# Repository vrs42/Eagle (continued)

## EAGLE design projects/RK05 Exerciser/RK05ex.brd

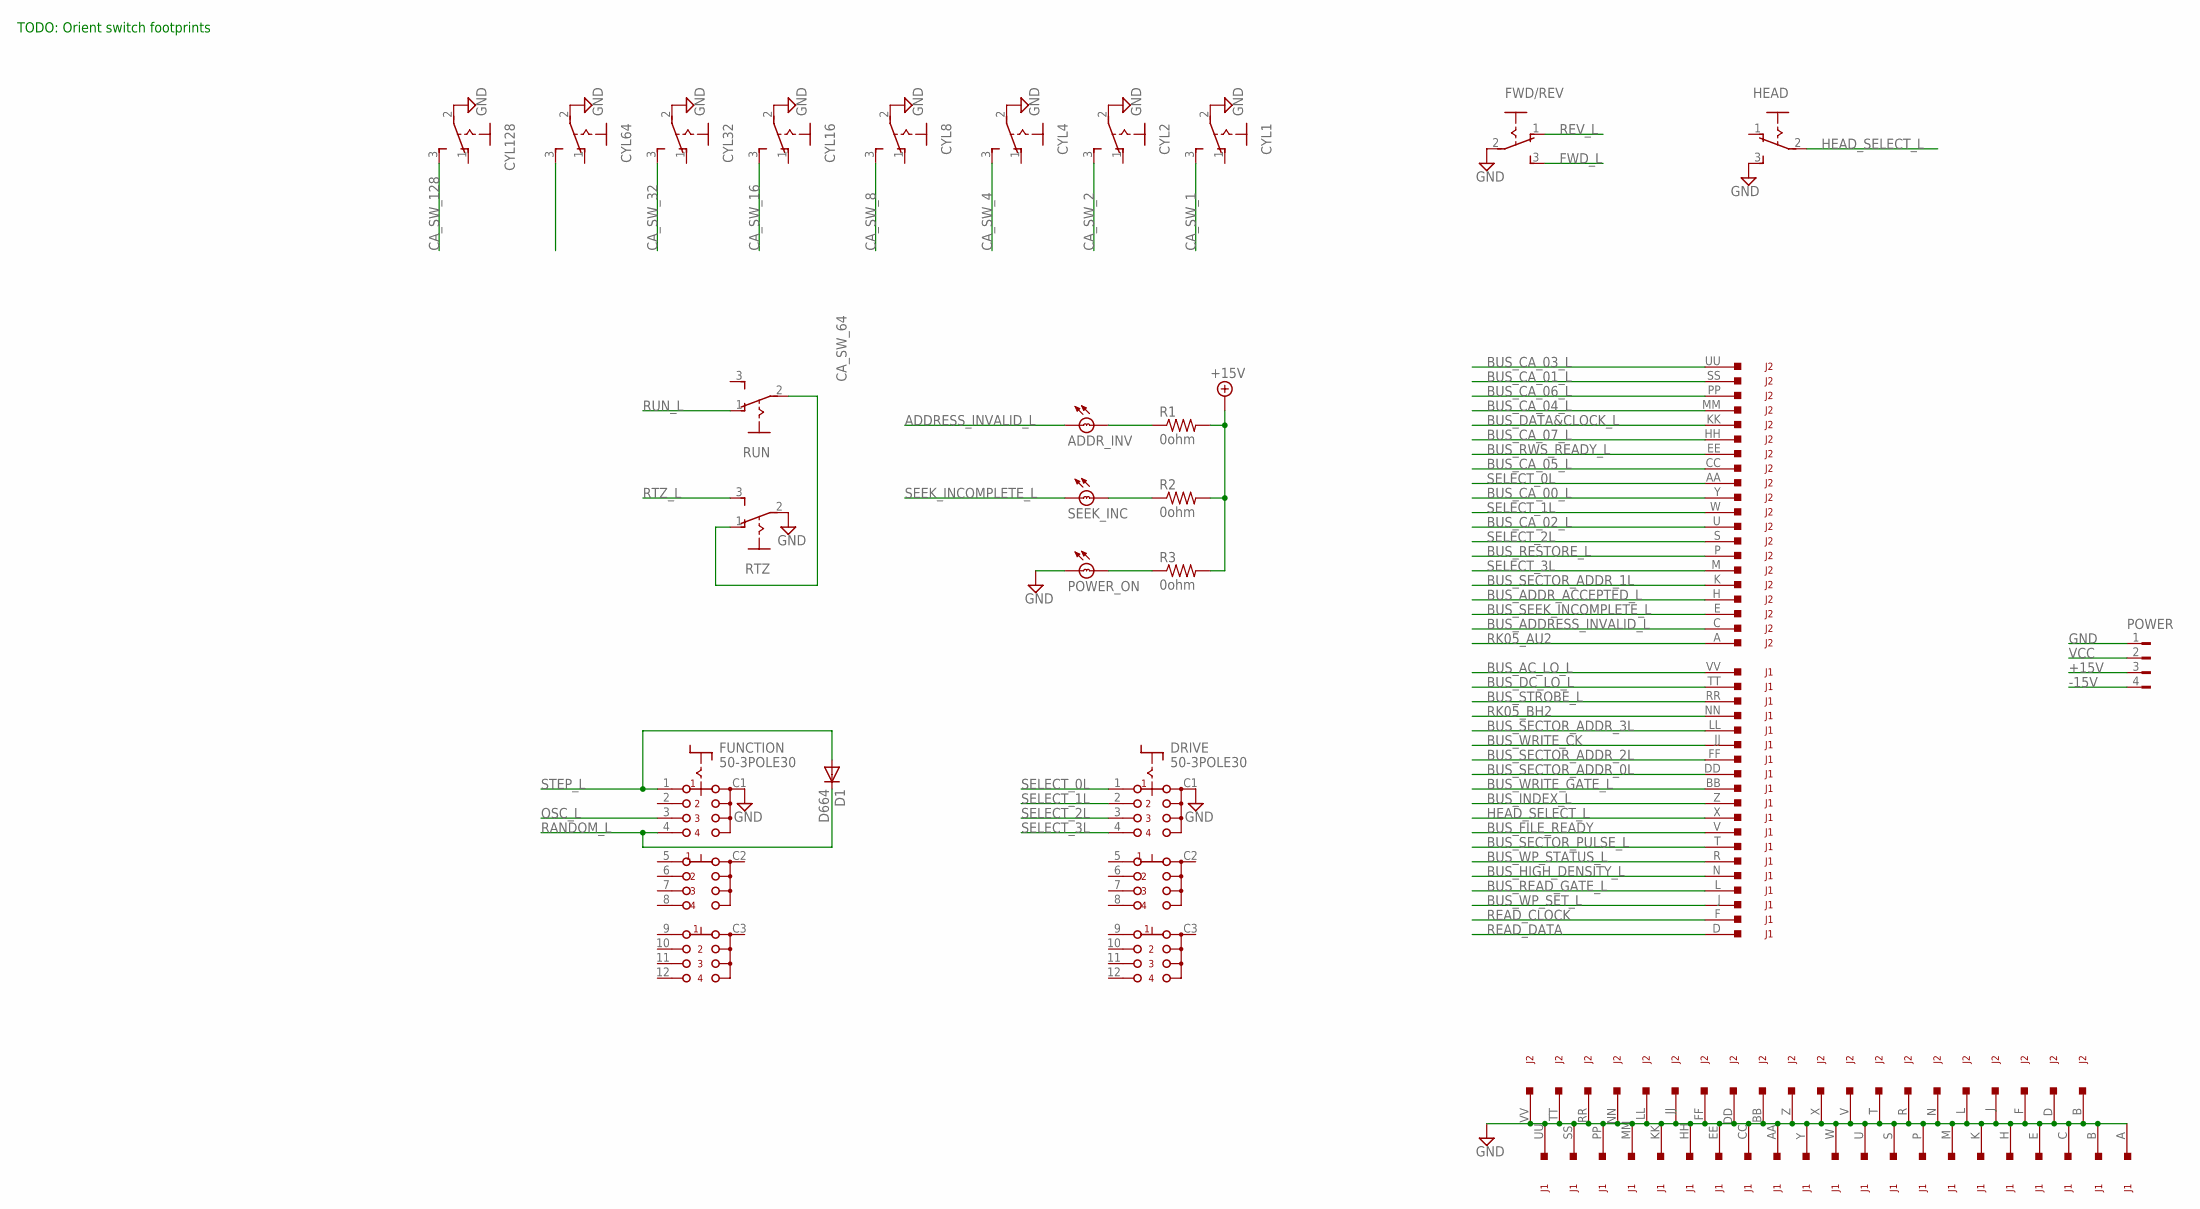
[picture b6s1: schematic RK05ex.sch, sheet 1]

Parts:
ADDR_INV: BULB
CYL1, CYL2, CYL4, CYL8, CYL16, CYL32, CYL64, CYL128: 255SB
D1: D664; DO35-10
DRIVE: 50-3POLE30
FUNCTION: 50-3POLE30
FWD/REV: 255SB
HEAD: 255SB
J1, J2: DEC40PINSV; DEC40PINV
POWER: FLOPPY-4
POWER_ON: BULB
R1, R2, R3: 0ohm; 0207/10
RTZ: 255SB
RUN: 255SB
SEEK_INC: BULB

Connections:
+15V: POWER.3, R1.2, R2.2, R3.2; also elsewhere on the board
-15V: POWER.4; also elsewhere on the board
ADDRESS_INVALID_L: ADDR_INV.B; also elsewhere on the board
BUS_AC_LO_L: J1.VV; also elsewhere on the board
BUS_ADDRESS_INVALID_L: J2.C; also elsewhere on the board
BUS_ADDR_ACCEPTED_L: J2.H; also elsewhere on the board
BUS_CA_00_L: J2.Y; also elsewhere on the board
BUS_CA_01_L: J2.SS; also elsewhere on the board
BUS_CA_02_L: J2.U; also elsewhere on the board
BUS_CA_03_L: J2.UU; also elsewhere on the board
BUS_CA_04_L: J2.MM; also elsewhere on the board
BUS_CA_05_L: J2.CC; also elsewhere on the board
BUS_CA_06_L: J2.PP; also elsewhere on the board
BUS_CA_07_L: J2.HH; also elsewhere on the board
BUS_DATA&CLOCK_L: J2.KK; also elsewhere on the board
BUS_DC_LO_L: J1.TT; also elsewhere on the board
BUS_FILE_READY: J1.V; also elsewhere on the board
BUS_HIGH_DENSITY_L: J1.N; also elsewhere on the board
BUS_INDEX_L: J1.Z; also elsewhere on the board
BUS_READ_GATE_L: J1.L; also elsewhere on the board
BUS_RESTORE_L: J2.P; also elsewhere on the board
BUS_RWS_READY_L: J2.EE; also elsewhere on the board
BUS_SECTOR_ADDR_0L: J1.DD; also elsewhere on the board
BUS_SECTOR_ADDR_1L: J2.K; also elsewhere on the board
BUS_SECTOR_ADDR_2L: J1.FF; also elsewhere on the board
BUS_SECTOR_ADDR_3L: J1.LL; also elsewhere on the board
BUS_SECTOR_PULSE_L: J1.T; also elsewhere on the board
BUS_SEEK_INCOMPLETE_L: J2.E; also elsewhere on the board
BUS_STROBE_L: J1.RR; also elsewhere on the board
BUS_WP_SET_L: J1.J; also elsewhere on the board
BUS_WP_STATUS_L: J1.R; also elsewhere on the board
BUS_WRITE_CK: J1.JJ; also elsewhere on the board
BUS_WRITE_GATE_L: J1.BB; also elsewhere on the board
CA_SW_1: CYL1.3 (S); also elsewhere on the board
CA_SW_2: CYL2.3 (S); also elsewhere on the board
CA_SW_4: CYL4.3 (S); also elsewhere on the board
CA_SW_8: CYL8.3 (S); also elsewhere on the board
CA_SW_16: CYL16.3 (S); also elsewhere on the board
CA_SW_32: CYL32.3 (S); also elsewhere on the board
CA_SW_64: CYL64.3 (S); also elsewhere on the board
CA_SW_128: CYL128.3 (S); also elsewhere on the board
FWD_L: FWD/REV.3 (S); also elsewhere on the board
GND: CYL1.2, CYL2.2, CYL4.2, CYL8.2, CYL16.2, CYL32.2, CYL64.2, CYL128.2, DRIVE.C1 (A), FUNCTION.C1 (A), FWD/REV.2, HEAD.3 (S), J1.A, J1.AA, J1.B, J1.C, J1.CC, J1.E, J1.EE, J1.H, J1.HH, J1.K, J1.KK, J1.M, J1.MM, J1.P, J1.PP, J1.S, J1.SS, J1.U, J1.UU, J1.W, J1.Y, J2.B, J2.BB, J2.D, J2.DD, J2.F, J2.FF, J2.J, J2.JJ, J2.L, J2.LL, J2.N, J2.NN, J2.R, J2.RR, J2.T, J2.TT, J2.V, J2.VV, J2.X, J2.Z, POWER.1, POWER_ON.B, RTZ.2; also elsewhere on the board
HEAD_SELECT_L: HEAD.2, J1.X; also elsewhere on the board
unnamed: RTZ.1 (O), RUN.2
unnamed: ADDR_INV.A, R1.1
unnamed: R2.1, SEEK_INC.A
unnamed: POWER_ON.A, R3.1
OSC_L: FUNCTION.3 (A3); also elsewhere on the board
RANDOM_L: D1.C, FUNCTION.4 (A4); also elsewhere on the board
READ_CLOCK: J1.F; also elsewhere on the board
READ_DATA: J1.D; also elsewhere on the board
REV_L: FWD/REV.1 (O); also elsewhere on the board
RK05_AU2: J2.A; also elsewhere on the board
RK05_BH2: J1.NN; also elsewhere on the board
RTZ_L: RTZ.3 (S); also elsewhere on the board
RUN_L: RUN.1 (O); also elsewhere on the board
SEEK_INCOMPLETE_L: SEEK_INC.B; also elsewhere on the board
SELECT_0L: DRIVE.1 (A1), J2.AA; also elsewhere on the board
SELECT_1L: DRIVE.2 (A2), J2.W; also elsewhere on the board
SELECT_2L: DRIVE.3 (A3), J2.S; also elsewhere on the board
SELECT_3L: DRIVE.4 (A4), J2.M; also elsewhere on the board
STEP_L: D1.A, FUNCTION.1 (A1); also elsewhere on the board
VCC: POWER.2; also elsewhere on the board

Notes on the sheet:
TODO: Orient switch footprints

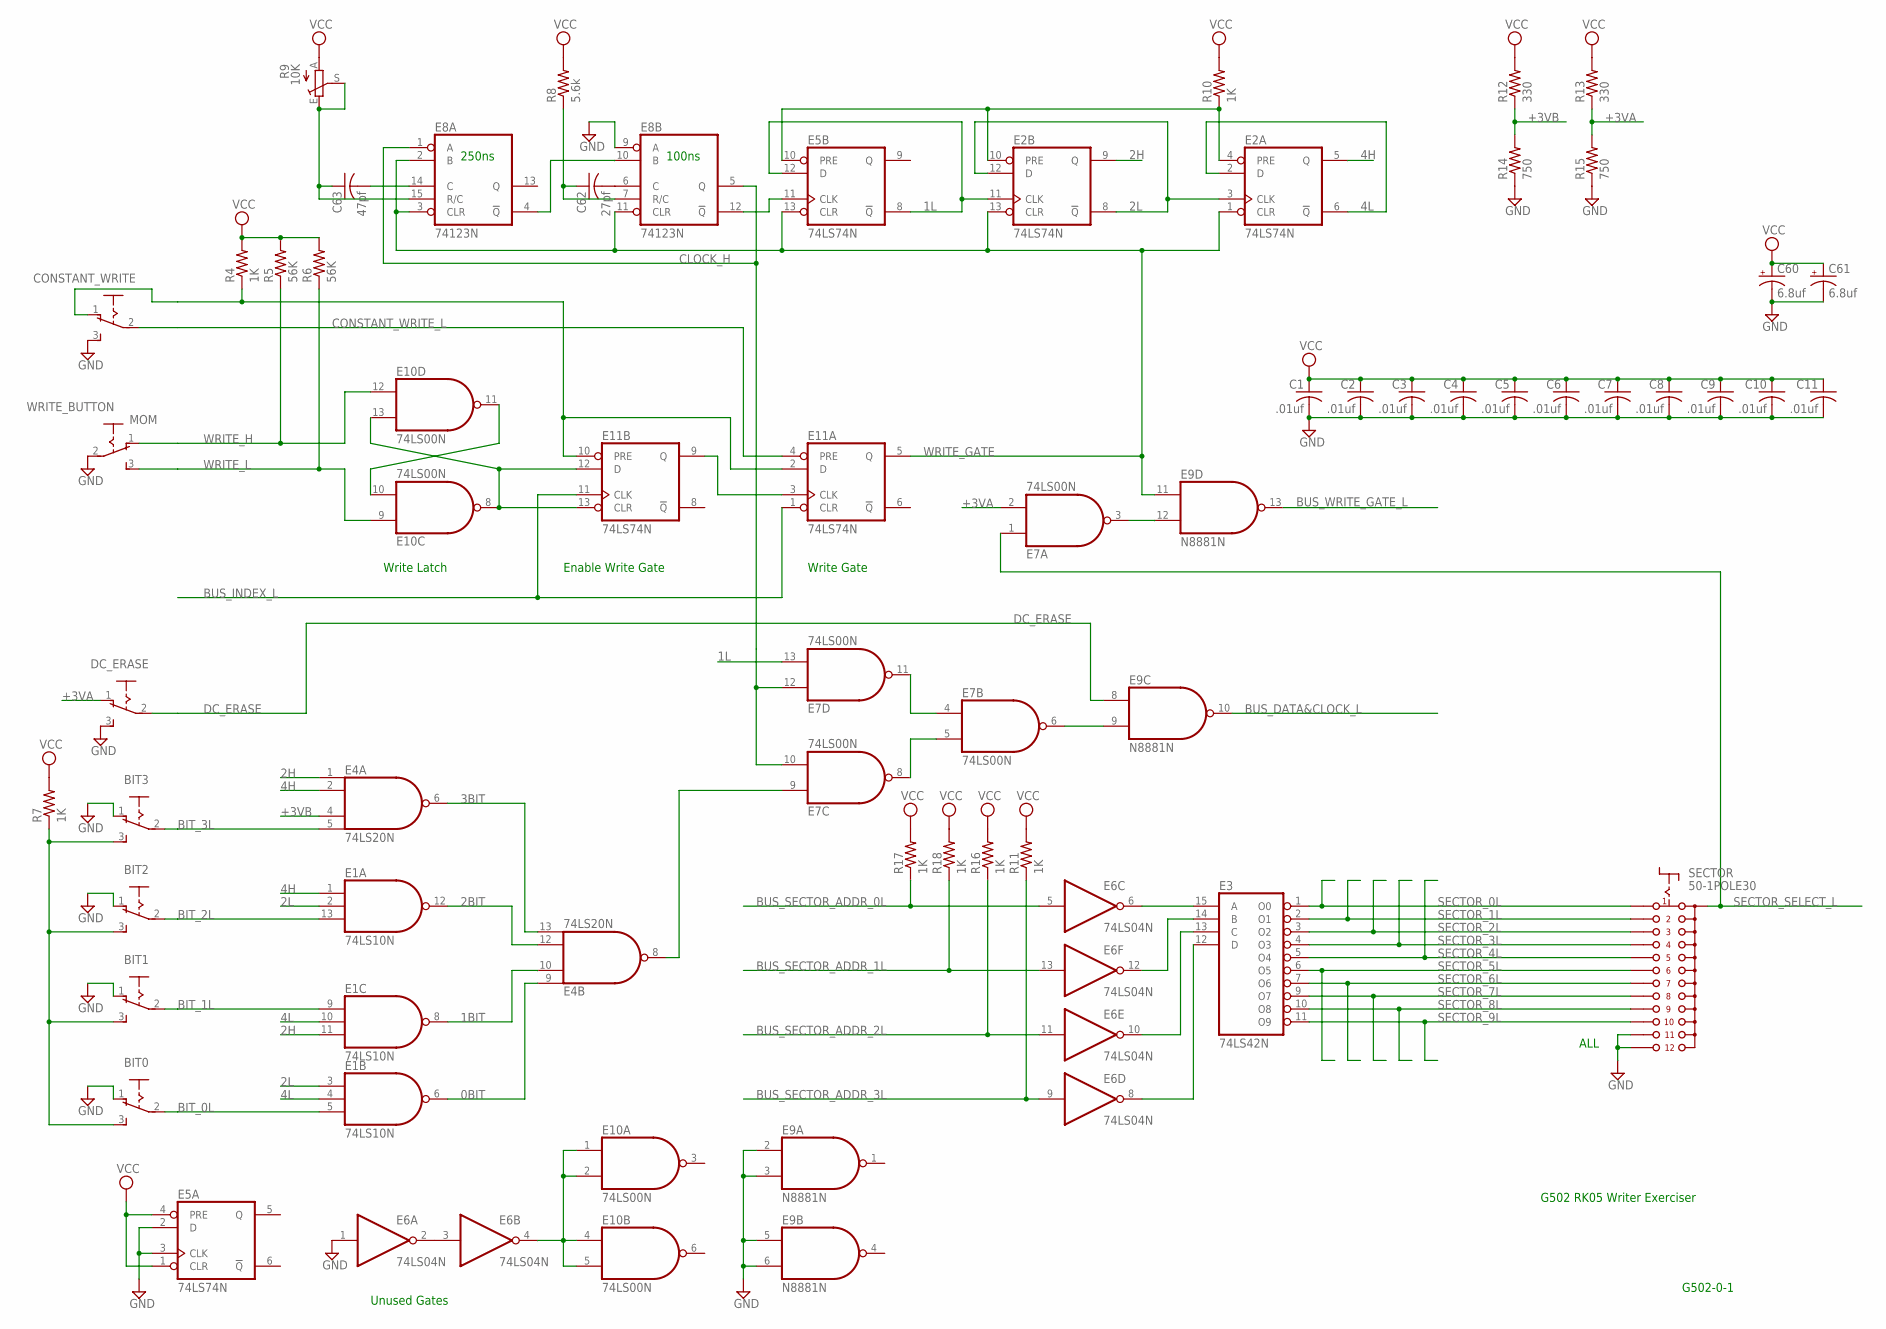
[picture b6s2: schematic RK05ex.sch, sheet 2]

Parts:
BIT0, BIT1, BIT2, BIT3: 255SB
C1, C2, C3, C4, C5, C6, C7, C8, C9, C10, C11: .01uf; C075-032X103
C60, C61: 6.8uf; E15-5
C62: 27pf; C075-032X103
C63: 47pf; C075-032X103
CONSTANT_WRITE: 255SB
DC_ERASE: 255SB
E1: 74LS10N; DIL14
E2, E5, E11: 74LS74N; DIL14
E3: 74LS42N; DIL16
E4: 74LS20N; DIL14
E6: 74LS04N; DIL14
E7, E10: 74LS00N; DIL14
E8: 74123N; DIL16
E9: N8881N; DIL14
R4, R7, R10, R11, R16, R17, R18: 1K; 0207/10
R5, R6: 56K; 0207/10
R8: 5.6k; 0207/10
R9: 10K; SP19L
R12, R13: 330; 0207/10
R14, R15: 750; 0207/10
SECTOR: 50-1POLE30
WRITE_BUTTON: MOM; 255SB

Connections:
0BIT: E1.6 (O), E4.9 (I0)
1.44MHZ: E5.11 (CLK), E8.12 (!Q)
1BIT: E1.8 (O), E4.10 (I1)
1L: E2.11 (CLK), E5.8 (!Q), E5.12 (D), E7.13 (I1)
2.88MHZ: E8.4 (!Q), E8.10 (B)
2BIT: E1.12 (O), E4.12 (I2)
2H: E1.11 (I2), E2.9 (Q), E4.1 (I0)
2L: E1.2 (I1), E1.3 (I0), E2.3 (CLK), E2.8 (!Q), E2.12 (D)
3BIT: E4.6 (O), E4.13 (I3)
4H: E1.1 (I0), E2.5 (Q), E4.2 (I1)
4L: E1.4 (I1), E1.10 (I1), E2.2 (D), E2.6 (!Q)
+3VA: DC_ERASE.1 (O), E7.2 (I1), R13.1, R15.2
+3VB: E4.4 (I2), R12.1, R14.2
+3VC: CONSTANT_WRITE.1 (O), E11.2 (D), E11.10 (PRE), R4.1
BIT_0L: BIT0.2, E1.5 (I2)
BIT_1L: BIT1.2, E1.9 (I0)
BIT_2L: BIT2.2, E1.13 (I2)
BIT_3L: BIT3.2, E4.5 (I3)
BUS_DATA&CLOCK_L: E9.10 (O); also elsewhere on the board
BUS_INDEX_L: E11.1 (CLR), E11.11 (CLK); also elsewhere on the board
BUS_SECTOR_ADDR_0L: E6.5 (I), R17.1; also elsewhere on the board
BUS_SECTOR_ADDR_1L: E6.13 (I), R18.1; also elsewhere on the board
BUS_SECTOR_ADDR_2L: E6.11 (I), R16.1; also elsewhere on the board
BUS_SECTOR_ADDR_3L: E6.9 (I), R11.1; also elsewhere on the board
BUS_WRITE_GATE_L: E9.13 (O); also elsewhere on the board
CLOCK_H: E7.10 (I1), E7.12 (I0), E8.1 (A), E8.5 (Q)
CONSTANT_WRITE_L: CONSTANT_WRITE.2, E11.4 (PRE)
DATA_BITS: BIT0.3 (S), BIT1.3 (S), BIT2.3 (S), BIT3.3 (S), R7.1
DC_ERASE: DC_ERASE.2, E9.8 (I0)
GND: BIT0.1 (O), BIT1.1 (O), BIT2.1 (O), BIT3.1 (O), C1.2, C2.2, C3.2, C4.2, C5.2, C6.2, C7.2, C8.2, C9.2, C10.2, C11.2, C60.-, C61.-, CONSTANT_WRITE.3 (S), DC_ERASE.3 (S), E1.7 (GND), E2.7 (GND), E3.8 (GND), E4.7 (GND), E5.2 (D), E5.3 (CLK), E5.7 (GND), E6.1 (I), E6.7 (GND), E7.7 (GND), E8.8 (GND), E8.9 (A), E9.2 (I0), E9.3 (I1), E9.5 (I0), E9.6 (I1), E9.7 (GND), E10.7 (GND), E11.7 (GND), R14.1, R15.1, SECTOR.11, SECTOR.12, WRITE_BUTTON.2; also elsewhere on the board
unnamed: E7.6 (O), E9.9 (I1)
unnamed: E10.8 (O), E10.13 (I1), E11.12 (D), E11.13 (CLR)
unnamed: E10.10 (I1), E10.11 (O)
unnamed: E2.4 (PRE), E2.10 (PRE), E5.10 (PRE), R10.1
unnamed: E7.4 (I0), E7.11 (O)
unnamed: E7.5 (I1), E7.8 (O)
unnamed: E11.3 (CLK), E11.9 (Q)
unnamed: E4.8 (O), E7.9 (I0)
unnamed: C63.2, E8.14 (C)
unnamed: C62.2, E8.6 (C)
unnamed: C63.1, E8.15 (R/C), R9.E, R9.S
unnamed: C62.1, E8.7 (R/C), R8.1
unnamed: E7.3 (O), E9.12 (I1)
unnamed: E3.15 (A), E6.6 (O)
unnamed: E3.14 (B), E6.12 (O)
unnamed: E3.13 (C), E6.10 (O)
unnamed: E3.12 (D), E6.8 (O)
unnamed: E6.2 (O), E6.3 (I)
unnamed: E6.4 (O), E10.1 (I0), E10.2 (I1), E10.4 (I0), E10.5 (I1)
SECTOR_0L: E3.1 (O0), SECTOR.1
SECTOR_1L: E3.2 (O1), SECTOR.2
SECTOR_2L: E3.3 (O2), SECTOR.3
SECTOR_3L: E3.4 (O3), SECTOR.4
SECTOR_4L: E3.5 (O4), SECTOR.5
SECTOR_5L: E3.6 (O5), SECTOR.6
SECTOR_6L: E3.7 (O6), SECTOR.7
SECTOR_7L: E3.9 (O7), SECTOR.8
SECTOR_8L: E3.10 (O8), SECTOR.9
SECTOR_9L: E3.11 (O9), SECTOR.10
SECTOR_SELECT_L: E7.1 (I0), SECTOR.C (A)
VCC: C1.1, C2.1, C3.1, C4.1, C5.1, C6.1, C7.1, C8.1, C9.1, C10.1, C11.1, C60.+, C61.+, E1.14 (VCC), E2.14 (VCC), E3.16 (VCC), E4.14 (VCC), E5.1 (CLR), E5.4 (PRE), E5.14 (VCC), E6.14 (VCC), E7.14 (VCC), E8.16 (VCC), E9.14 (VCC), E10.14 (VCC), E11.14 (VCC), R4.2, R5.2, R6.2, R7.2, R8.2, R9.A, R10.2, R11.2, R12.2, R13.2, R16.2, R17.2, R18.2; also elsewhere on the board
WRITE_GATE: E2.1 (CLR), E2.13 (CLR), E5.13 (CLR), E8.2 (B), E8.3 (CLR), E8.11 (CLR), E9.11 (I0), E11.5 (Q)
WRITE_H: E10.12 (I0), R5.1, WRITE_BUTTON.1 (O)
WRITE_L: E10.9 (I0), R6.1, WRITE_BUTTON.3 (S)

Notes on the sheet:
Write Latch
Enable Write Gate
Write Gate
250ns
100ns
ALL
Unused Gates
G502 RK05 Writer Exerciser
G502-0-1

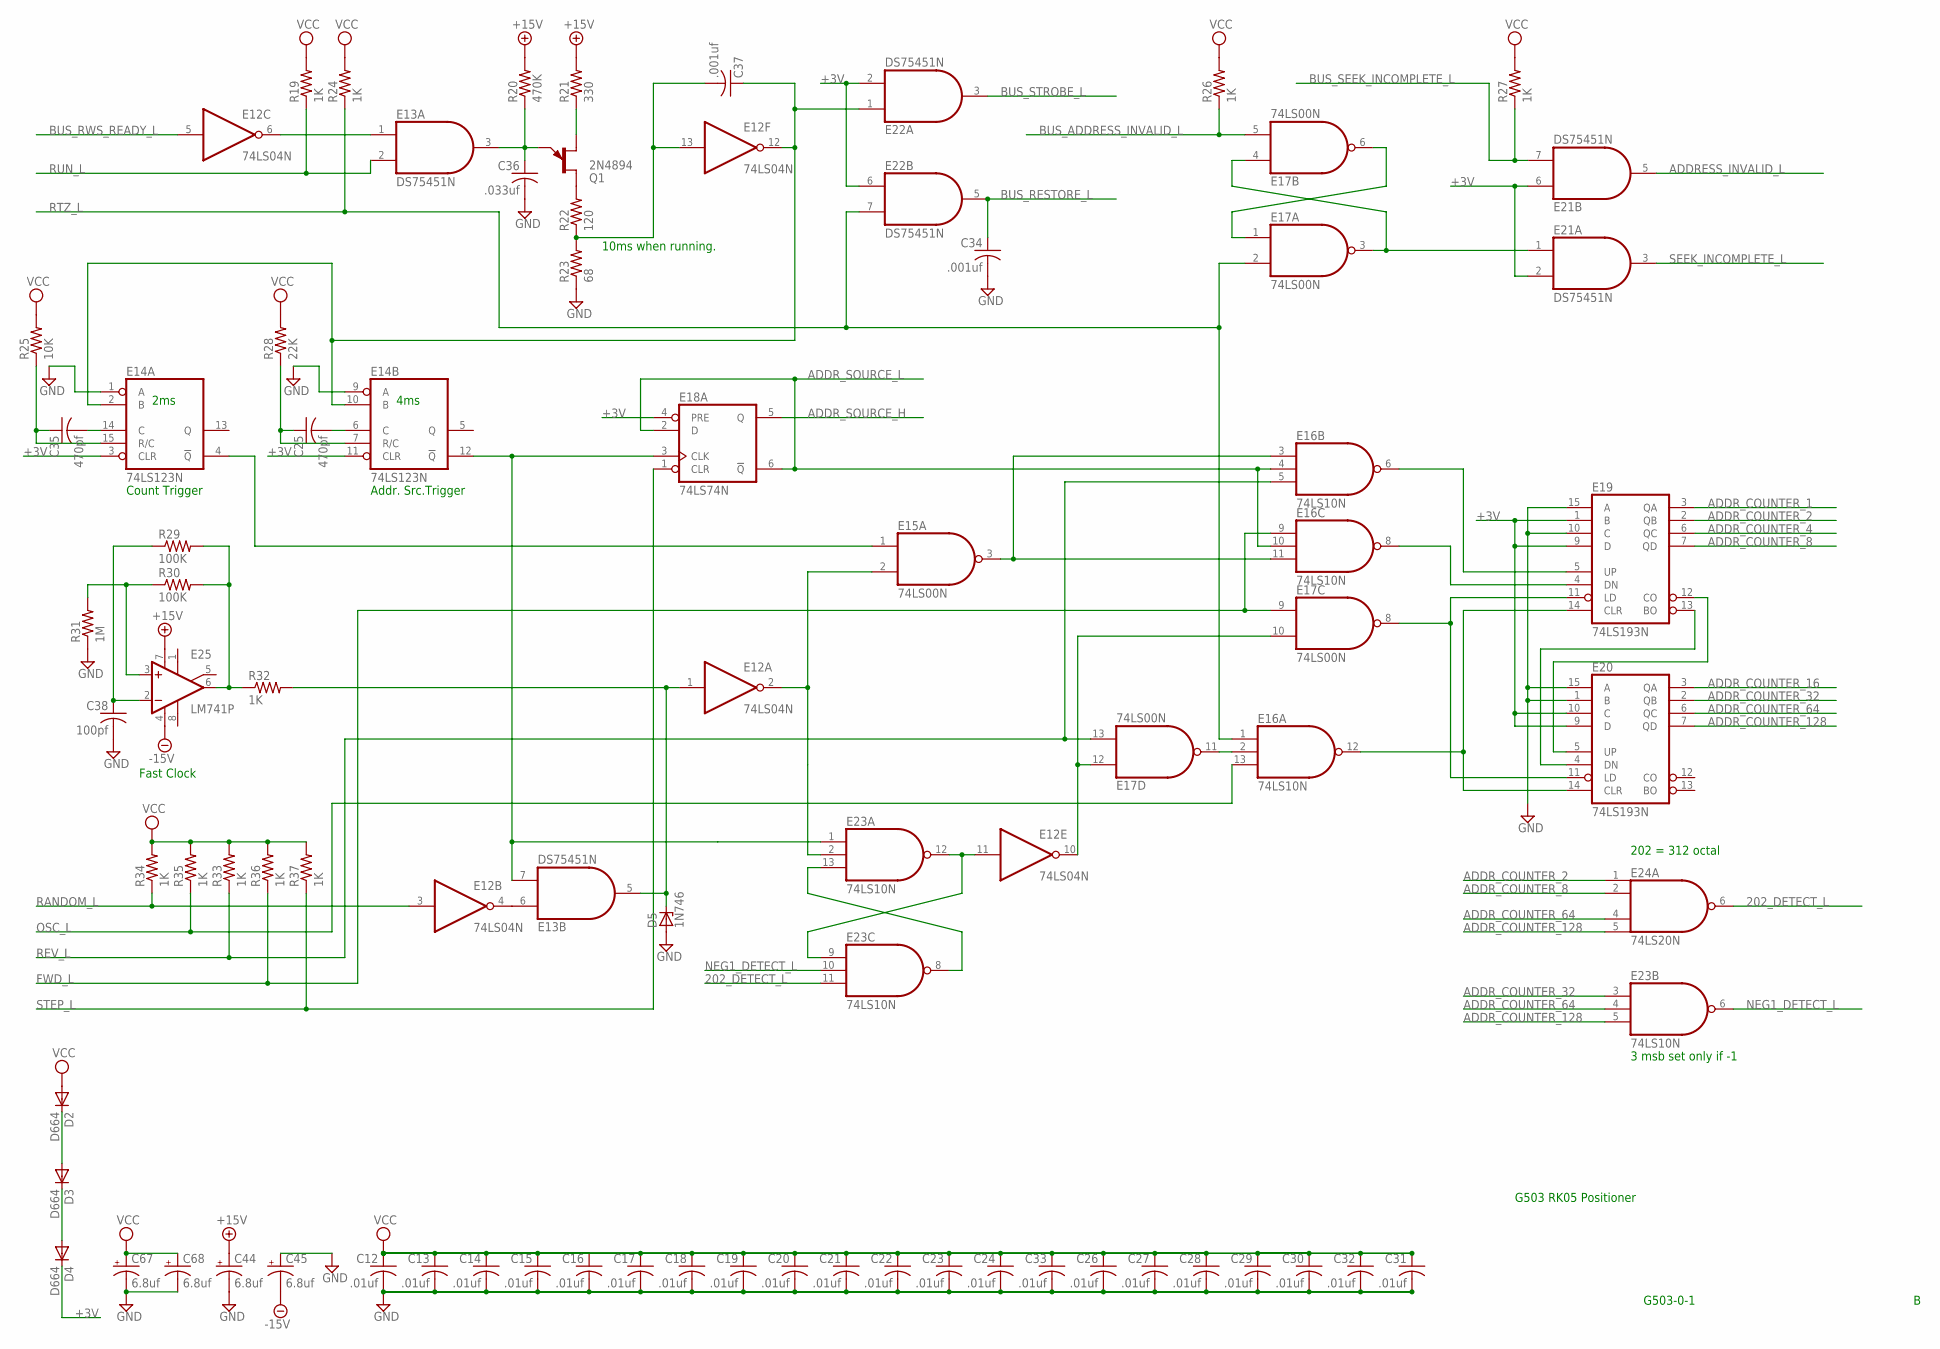
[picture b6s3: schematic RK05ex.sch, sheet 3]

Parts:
C12, C13, C14, C15, C16, C17, C18, C19, C20, C21, C22, C23, C24, C26, C27, C28, C29, C30, C31, C32, C33: .01uf; C075-032X103
C25, C35: 470pf; C075-032X103
C34, C37: .001uf; C075-032X103
C36: .033uf; C075-032X103
C38: 100pf; C075-032X103
C44, C45, C67, C68: 6.8uf; E15-5
D2, D3, D4: D664; DO35-10
D5: 1N746; DO35Z10
E12: 74LS04N; DIL14
E13, E21, E22: DS75451N; DIL08
E14: 74LS123N; DIL16
E15, E17: 74LS00N; DIL14
E16, E23: 74LS10N; DIL14
E18: 74LS74N; DIL14
E19, E20: 74LS193N; DIL16
E24: 74LS20N; DIL14
E25: LM741P; DIL08
Q1: 2N4894; TO92E
R19, R24, R26, R27, R32, R33, R34, R35, R36, R37: 1K; 0207/10
R20: 470K; 0207/10
R21: 330; 0207/10
R22: 120; 0207/10
R23: 68; 0207/10
R25: 10K; 0207/10
R28: 22K; 0207/10
R29, R30: 100K; 0207/10
R31: 1M; 0207/10

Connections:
202_DETECT_L: E23.11 (I2), E24.6 (O)
+3V: D4.C, E14.3 (CLR), E14.11 (CLR), E18.4 (PRE), E19.1 (B), E19.9 (D), E20.9 (D), E20.10 (C), E21.2 (I1), E21.6 (I0), E22.2 (I1), E22.6 (I0)
+15V: C44.+, E25.7 (V+), R20.2, R21.2; also elsewhere on the board
-15V: C45.-, E25.4 (V-); also elsewhere on the board
ADDRESS_INVALID_L: E21.5 (O); also elsewhere on the board
ADDR_COUNTER_1: E19.3 (QA); also elsewhere on the board
ADDR_COUNTER_2: E19.2 (QB), E24.1 (I0); also elsewhere on the board
ADDR_COUNTER_4: E19.6 (QC); also elsewhere on the board
ADDR_COUNTER_8: E19.7 (QD), E24.2 (I1); also elsewhere on the board
ADDR_COUNTER_16: E20.3 (QA); also elsewhere on the board
ADDR_COUNTER_32: E20.2 (QB), E23.3 (I0); also elsewhere on the board
ADDR_COUNTER_64: E20.6 (QC), E23.4 (I1), E24.4 (I2); also elsewhere on the board
ADDR_COUNTER_128: E20.7 (QD), E23.5 (I2), E24.5 (I3); also elsewhere on the board
ADDR_SOURCE_H: E18.5 (Q); also elsewhere on the board
ADDR_SOURCE_L: E16.4 (I1), E16.10 (I1), E18.2 (D), E18.6 (!Q); also elsewhere on the board
BUS_ADDRESS_INVALID_L: E17.5 (I1), R26.1; also elsewhere on the board
BUS_RESTORE_L: C34.1, E22.5 (O); also elsewhere on the board
BUS_RWS_READY_L: E12.5 (I); also elsewhere on the board
BUS_SEEK_INCOMPLETE_L: E21.7 (I1), R27.1; also elsewhere on the board
BUS_STROBE_L: E22.3 (O); also elsewhere on the board
FWD_L: E16.9 (I0), E17.9 (I0), R36.1; also elsewhere on the board
GND: C12.2, C13.2, C14.2, C15.2, C16.2, C17.2, C18.2, C19.2, C20.2, C21.2, C22.2, C23.2, C24.2, C26.2, C27.2, C28.2, C29.2, C30.2, C31.2, C32.2, C33.2, C34.2, C36.2, C38.2, C44.-, C45.+, C67.-, C68.-, D5.A, E12.7 (GND), E13.4 (GND), E14.1 (A), E14.8 (GND), E14.9 (A), E15.7 (GND), E16.7 (GND), E17.7 (GND), E18.7 (GND), E19.8 (GND), E19.10 (C), E19.15 (A), E20.1 (B), E20.8 (GND), E20.15 (A), E21.4 (GND), E22.4 (GND), E23.7 (GND), E24.7 (GND), R23.1, R31.1; also elsewhere on the board
unnamed: E12.6 (O), E13.1 (I0)
unnamed: C36.1, E13.3 (O), Q1.E, R20.1
unnamed: Q1.B1, R21.1
unnamed: Q1.B2, R22.2
unnamed: C37.2, E12.13 (I), R22.1, R23.2
unnamed: C37.1, E12.12 (O), E14.2 (B), E14.10 (B), E22.1 (I0)
unnamed: E17.1 (I0), E17.6 (O)
unnamed: E17.3 (O), E17.4 (I0), E21.1 (I0)
unnamed: C35.1, E14.15 (R/C), R25.1
unnamed: C35.2, E14.14 (C)
unnamed: C25.1, E14.7 (R/C), R28.1
unnamed: C25.2, E14.6 (C)
unnamed: E19.13 (BO), E20.4 (DN)
unnamed: E19.12 (CO), E20.5 (UP)
unnamed: E16.6 (O), E19.5 (UP)
unnamed: E16.8 (O), E19.4 (DN)
unnamed: E17.8 (O), E19.11 (LD), E20.11 (LD)
unnamed: E16.12 (O), E19.14 (CLR), E20.14 (CLR)
unnamed: C38.1, E25.2 (-IN), R29.1
unnamed: E25.6 (OUT), R29.2, R30.2, R32.1
unnamed: E25.3 (+IN), R30.1, R31.2
unnamed: E12.2 (O), E15.2 (I1), E23.2 (I1)
unnamed: E14.4 (!Q), E15.1 (I0)
unnamed: D2.C, D3.A
unnamed: D3.C, D4.A
unnamed: E12.4 (O), E13.6 (I0)
unnamed: E13.7 (I1), E14.12 (!Q), E18.3 (CLK), E23.1 (I0)
unnamed: D5.C, E12.1 (I), E13.5 (O), R32.2
unnamed: E15.3 (O), E16.3 (I0), E16.11 (I2)
unnamed: E23.8 (O), E23.13 (I2)
unnamed: E12.11 (I), E23.9 (I0), E23.12 (O)
unnamed: E16.2 (I1), E17.11 (O)
unnamed: E12.10 (O), E17.10 (I1), E17.12 (I0)
NEG1_DETECT_L: E23.6 (O), E23.10 (I1)
OSC_L: E16.13 (I2), R35.1; also elsewhere on the board
RANDOM_L: E12.3 (I), R34.1; also elsewhere on the board
REV_L: E16.5 (I2), E17.13 (I1), R33.1; also elsewhere on the board
RTZ_L: E16.1 (I0), E17.2 (I1), E22.7 (I1), R24.1; also elsewhere on the board
RUN_L: E13.2 (I1), R19.1; also elsewhere on the board
SEEK_INCOMPLETE_L: E21.3 (O); also elsewhere on the board
STEP_L: E18.1 (CLR), R37.1; also elsewhere on the board
VCC: C12.1, C13.1, C14.1, C15.1, C16.1, C17.1, C18.1, C19.1, C20.1, C21.1, C22.1, C23.1, C24.1, C26.1, C27.1, C28.1, C29.1, C30.1, C31.1, C32.1, C33.1, C67.+, C68.+, D2.A, E12.14 (VCC), E13.8 (VCC), E14.16 (VCC), E15.14 (VCC), E16.14 (VCC), E17.14 (VCC), E18.14 (VCC), E19.16 (VCC), E20.16 (VCC), E21.8 (VCC), E22.8 (VCC), E23.14 (VCC), E24.14 (VCC), R19.2, R24.2, R25.2, R26.2, R27.2, R28.2, R33.2, R34.2, R35.2, R36.2, R37.2; also elsewhere on the board

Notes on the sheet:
2ms
4ms
Count Trigger
Addr. Src.Trigger
202 = 312 octal
3 msb set only if -1
Fast Clock
G503 RK05 Positioner
G503-0-1
10ms when running.

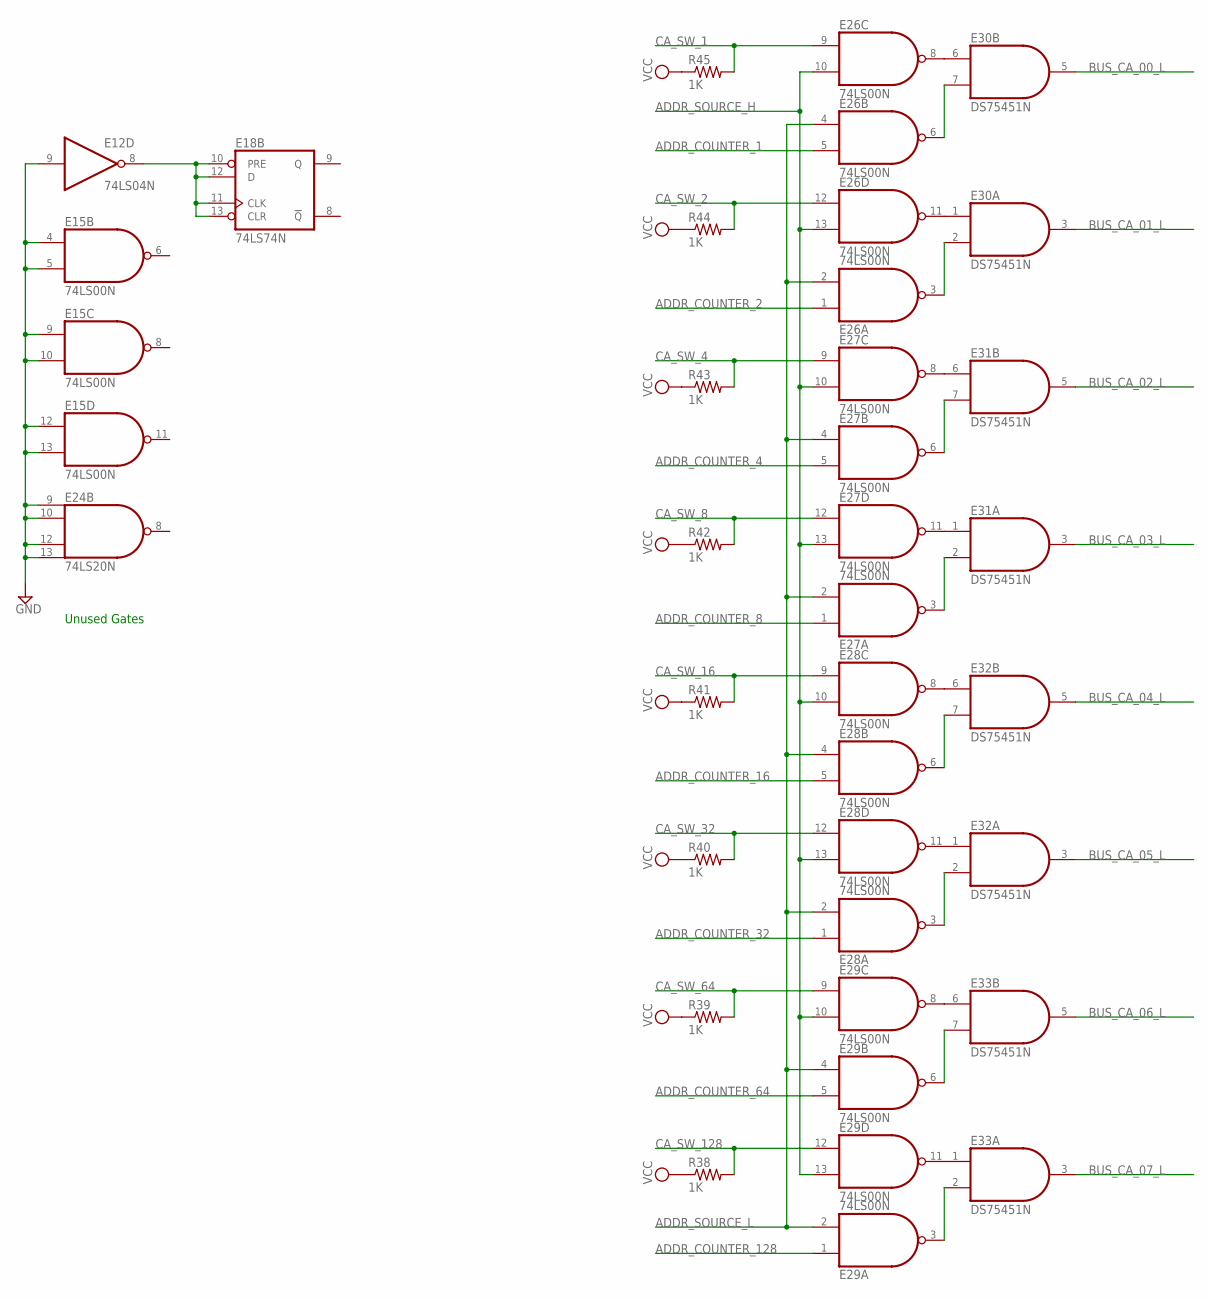
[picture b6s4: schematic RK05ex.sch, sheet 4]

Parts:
E12: 74LS04N; DIL14
E15, E26, E27, E28, E29: 74LS00N; DIL14
E18: 74LS74N; DIL14
E24: 74LS20N; DIL14
E30, E31, E32, E33: DS75451N; DIL08
R38, R39, R40, R41, R42, R43, R44, R45: 1K; 0207/10

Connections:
ADDR_COUNTER_1: E26.5 (I1); also elsewhere on the board
ADDR_COUNTER_2: E26.1 (I0); also elsewhere on the board
ADDR_COUNTER_4: E27.5 (I1); also elsewhere on the board
ADDR_COUNTER_8: E27.1 (I0); also elsewhere on the board
ADDR_COUNTER_16: E28.5 (I1); also elsewhere on the board
ADDR_COUNTER_32: E28.1 (I0); also elsewhere on the board
ADDR_COUNTER_64: E29.5 (I1); also elsewhere on the board
ADDR_COUNTER_128: E29.1 (I0); also elsewhere on the board
ADDR_SOURCE_H: E26.10 (I1), E26.13 (I1), E27.10 (I1), E27.13 (I1), E28.10 (I1), E28.13 (I1), E29.10 (I1), E29.13 (I1); also elsewhere on the board
ADDR_SOURCE_L: E26.2 (I1), E26.4 (I0), E27.2 (I1), E27.4 (I0), E28.2 (I1), E28.4 (I0), E29.2 (I1), E29.4 (I0); also elsewhere on the board
BUS_CA_00_L: E30.5 (O); also elsewhere on the board
BUS_CA_01_L: E30.3 (O); also elsewhere on the board
BUS_CA_02_L: E31.5 (O); also elsewhere on the board
BUS_CA_03_L: E31.3 (O); also elsewhere on the board
BUS_CA_04_L: E32.5 (O); also elsewhere on the board
BUS_CA_05_L: E32.3 (O); also elsewhere on the board
BUS_CA_06_L: E33.5 (O); also elsewhere on the board
BUS_CA_07_L: E33.3 (O); also elsewhere on the board
CA_SW_1: E26.9 (I0), R45.2; also elsewhere on the board
CA_SW_2: E26.12 (I0), R44.2; also elsewhere on the board
CA_SW_4: E27.9 (I0), R43.2; also elsewhere on the board
CA_SW_8: E27.12 (I0), R42.2; also elsewhere on the board
CA_SW_16: E28.9 (I0), R41.2; also elsewhere on the board
CA_SW_32: E28.12 (I0), R40.2; also elsewhere on the board
CA_SW_64: E29.9 (I0), R39.2; also elsewhere on the board
CA_SW_128: E29.12 (I0), R38.2; also elsewhere on the board
GND: E12.7 (GND), E12.9 (I), E15.4 (I0), E15.5 (I1), E15.7 (GND), E15.9 (I0), E15.10 (I1), E15.12 (I0), E15.13 (I1), E18.7 (GND), E24.7 (GND), E24.9 (I0), E24.10 (I1), E24.12 (I2), E24.13 (I3), E26.7 (GND), E27.7 (GND), E28.7 (GND), E29.7 (GND), E30.4 (GND), E31.4 (GND), E32.4 (GND), E33.4 (GND); also elsewhere on the board
unnamed: E26.6 (O), E30.7 (I1)
unnamed: E26.8 (O), E30.6 (I0)
unnamed: E26.3 (O), E30.2 (I1)
unnamed: E26.11 (O), E30.1 (I0)
unnamed: E27.8 (O), E31.6 (I0)
unnamed: E27.6 (O), E31.7 (I1)
unnamed: E27.11 (O), E31.1 (I0)
unnamed: E27.3 (O), E31.2 (I1)
unnamed: E28.6 (O), E32.7 (I1)
unnamed: E28.3 (O), E32.2 (I1)
unnamed: E29.6 (O), E33.7 (I1)
unnamed: E29.3 (O), E33.2 (I1)
unnamed: E29.11 (O), E33.1 (I0)
unnamed: E29.8 (O), E33.6 (I0)
unnamed: E28.11 (O), E32.1 (I0)
unnamed: E28.8 (O), E32.6 (I0)
unnamed: E12.8 (O), E18.10 (PRE), E18.11 (CLK), E18.12 (D), E18.13 (CLR)
VCC: E12.14 (VCC), E15.14 (VCC), E18.14 (VCC), E24.14 (VCC), E26.14 (VCC), E27.14 (VCC), E28.14 (VCC), E29.14 (VCC), E30.8 (VCC), E31.8 (VCC), E32.8 (VCC), E33.8 (VCC), R38.1, R39.1, R40.1, R41.1, R42.1, R43.1, R44.1, R45.1; also elsewhere on the board

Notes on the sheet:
Unused Gates
